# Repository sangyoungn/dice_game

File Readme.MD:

Thank you for visiting my humble work of hobby electronics.
This work is electronic dice game implemented with LEDs.

# Prerequisite 

## Hardware

* EFR32MG24 Explorer Kit
  * Can be replaced with any hardware which supports CircuitPython
* 7x LEDs
* 6x 1K Resistors
* 1x 10K Resistor
* 1x Push Button

## Software

* Simplicity Commander
* Thorny

# Directories

* ./hardware
  * KiCad Work
* ./code
  * CircuitPython code
* Readme.MD
  * This file
* schematic.pdf
* connection+diagram.pdf
  * Component connection diagram
* LICENSE

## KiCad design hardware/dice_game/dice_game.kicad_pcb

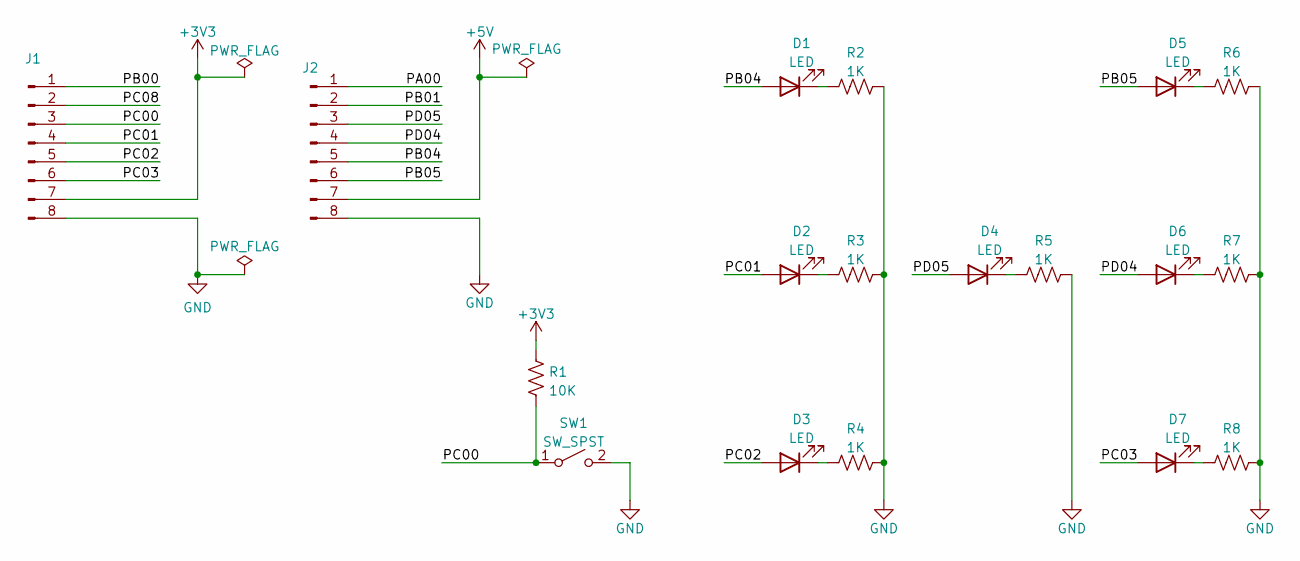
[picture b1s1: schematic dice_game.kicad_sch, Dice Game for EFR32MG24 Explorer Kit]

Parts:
D1, D2, D3, D4, D5, D6, D7: LED
J1, J2: Conn_01x08_Male
R1: 10K
R2, R3, R4, R5, R6, R7, R8: 1K
SW1: SW_SPST

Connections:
+3V3: J1.7, R1.1
+5V: J2.7
/PA00: J2.1
/PB00: J1.1
/PB01: J2.2
/PB04: D1.2 (A), J2.5
/PB05: D5.2 (A), J2.6
/PC00: J1.3, R1.2, SW1.1 (A)
/PC01: D2.2 (A), J1.4
/PC02: D3.2 (A), J1.5
/PC03: D7.2 (A), J1.6
/PC08: J1.2
/PD04: D6.2 (A), J2.4
/PD05: D4.2 (A), J2.3
GND: J1.8, J2.8, R2.2, R3.2, R4.2, R5.2, R6.2, R7.2, R8.2, SW1.2 (B)
unnamed: D1.1 (K), R2.1
unnamed: D2.1 (K), R3.1
unnamed: D3.1 (K), R4.1
unnamed: D4.1 (K), R5.1
unnamed: D5.1 (K), R6.1
unnamed: D6.1 (K), R7.1
unnamed: D7.1 (K), R8.1

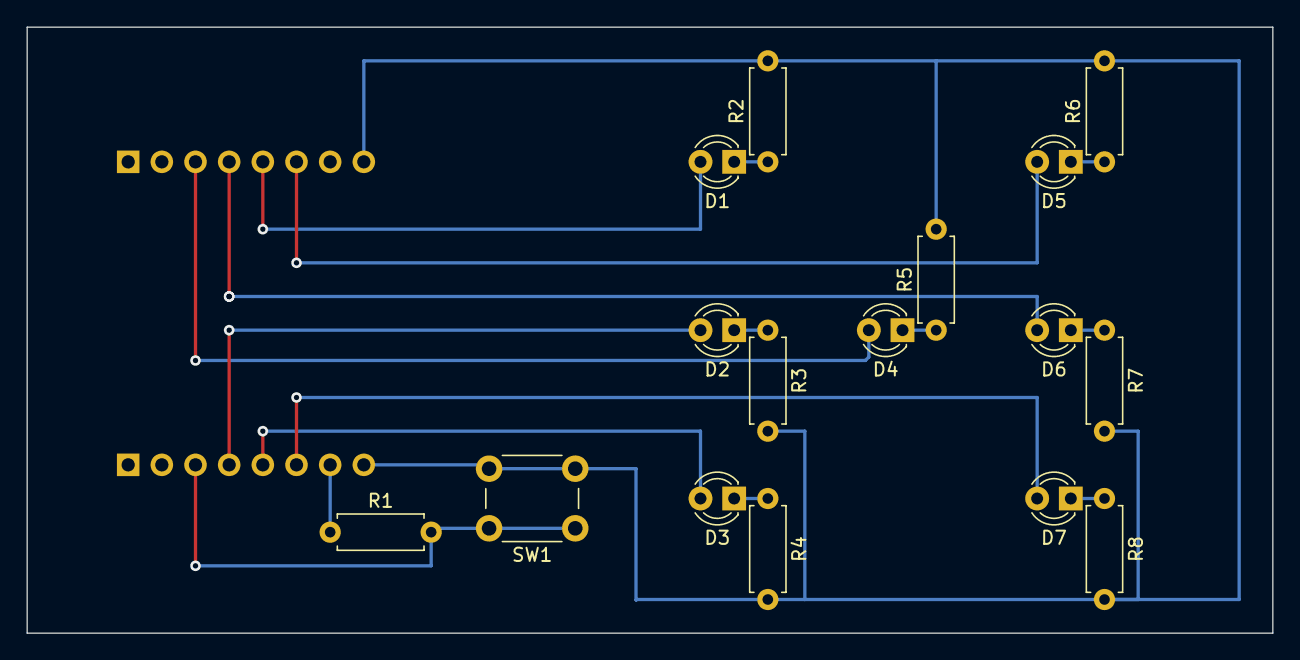
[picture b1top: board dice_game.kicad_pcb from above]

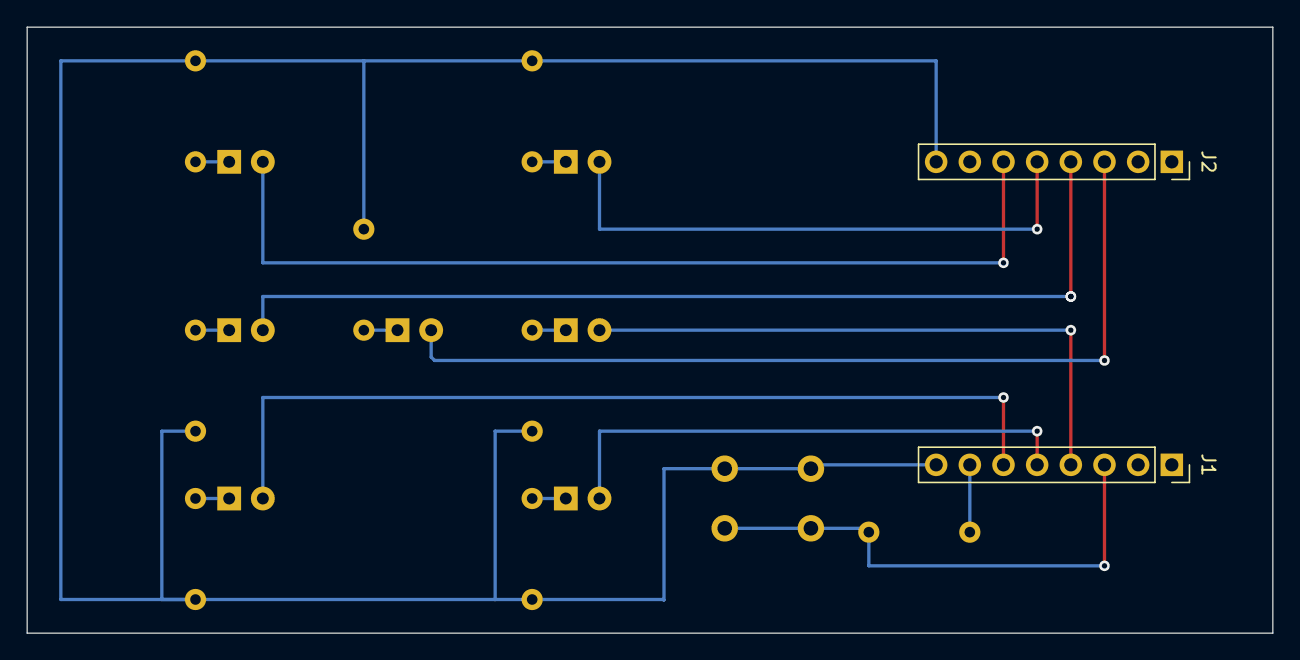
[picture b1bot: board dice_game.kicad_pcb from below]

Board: 2 copper layers, 94.0 x 45.7 mm, 18 parts (2 on the bottom side), 17 nets.

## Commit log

2024-08-04 Added License notice
2024-08-18 Fixed a logical bug in dice_game.py
